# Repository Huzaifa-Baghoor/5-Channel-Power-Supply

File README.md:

# Discreete Dual Output DC Power Supply
This is a Custom Designed 5 Channel DC power supply that provides 15V, 12V, 9V, 5V and 3.3V outputs.

## Working
The circuit takes AC input from Wall Socket and steps it down to 12V then this AC voltage is rectified be 1N4007 Diodes. This 12V DC voltage then goes to a capacitor which decreases the noise and the voltage goes to about 17V. then this voltage is passed through capacitors and zener diodes to provide the 15V, 12V, 9V, 5V and 3.3V outputs.

## Simulation
This Project is Simulated and Tested in Multisim. It worked fine there and supplied constant voltage under Load.

## PCB and Connections
I designed a Custom PCB for this project.

|Schematics|Tracks|
| :---: | :---: |
|  |  |

## 3D Case

I also designed a 3D enclosure box for the project that would have 11 holes, 1 for input and 10 for the outputs.

|View 1|View 2|
| :---: | :---: |
|  |  |

## How to Assemble

To Assemble the PCB, First get the PCB Fabricated and then Solder all the components into their dedicated places.

## BOM

| Name | Purpose | Quantity | Total Cost (USD) | Link | Distributor |
| :---: | :---: | :---: | :---: | :---: | :---: |
| TIP41C | Transistors | 5 | 7 | [TIP41C](https://www.aliexpress.com/item/1005009291854290.html?spm=a2g0o.productlist.main.2.2f5912668WryOQ&algo_pvid=0b7901ac-a991-4423-bff1-2842cce08b4d&algo_exp_id=0b7901ac-a991-4423-bff1-2842cce08b4d-1&pdp_ext_f=%7B%22order%22%3A%223%22%2C%22eval%22%3A%221%22%2C%22fromPage%22%3A%22search%22%7D&pdp_npi=6%40dis%21PKR%212005.10%211963.63%21%21%2143.52%2142.62%21%4021410daa17850251856081765e1e4e%2112000048636612928%21sea%21PK%212961473668%21X%211%210%21n_tag%3A-29919%3Bd%3A7347b7cd%3Bm03_new_user%3A-29895&curPageLogUid=xaTx0ebZWlhw&utparam-url=scene%3Asearch%7Cquery_from%3A%7Cx_object_id%3A1005009291854290%7C_p_origin_prod%3A) | AliExpress |
| Capacitors | Reducing Noise | 11 | 10 |  | AliExpress |
| Resistor | Resistance | 6 | 8 | [Resistor](https://www.aliexpress.com/item/1005006898731441.html?spm=a2g0o.productlist.main.2.5adb174e6BrR4E&algo_pvid=a8b488c6-4e8d-4539-8e68-136df8322c2e&algo_exp_id=a8b488c6-4e8d-4539-8e68-136df8322c2e-1&pdp_ext_f=%7B%22order%22%3A%2218454%22%2C%22spu_best_type%22%3A%22price%22%2C%22eval%22%3A%221%22%2C%22fromPage%22%3A%22search%22%7D&pdp_npi=6%40dis%21PKR%21700.27%21540.04%21%21%2115.19%2111.71%21%40213ba0c517805536286016955e1c85%2112000038655131992%21sea%21PK%212961473668%21X%211%210%21n_tag%3A-29919%3Bd%3A7347b7cd%3Bm03_new_user%3A-29895%3BpisId%3A5000000208499468&curPageLogUid=xK5nH0KMlH7Z&utparam-url=scene%3Asearch%7Cquery_from%3A%7Cx_object_id%3A1005006898731441%7C_p_origin_prod%3A) | AliExpress |
| 12v Transformer | Stepping Down 220V to 12V | 1 | 7 | [12v Transformer](https://www.aliexpress.com/item/1005002190993881.html?spm=a2g0o.productlist.main.3.5ab7c57cYfLk9E&algo_pvid=73899792-524f-4ba5-b0be-0d52e075c67c&algo_exp_id=73899792-524f-4ba5-b0be-0d52e075c67c-2&pdp_ext_f=%7B%22order%22%3A%2269%22%2C%22spu_best_type%22%3A%22price%22%2C%22eval%22%3A%221%22%2C%22fromPage%22%3A%22search%22%7D&pdp_npi=6%40dis%21PKR%212058.51%211933.56%21%21%216.59%216.19%21%40212e520d17805533749515631efcd4%2112000019002828064%21sea%21PK%212961473668%21X%211%210%21n_tag%3A-29919%3Bd%3A7347b7cd%3Bm03_new_user%3A-29895&curPageLogUid=AV8pa8Zxzb4a&utparam-url=scene%3Asearch%7Cquery_from%3A%7Cx_object_id%3A1005002190993881%7C_p_origin_prod%3A) | AliExpress |
| Diode | Rectifier | 1 | 3.6 | [Diode](https://www.aliexpress.com/item/1005012369097375.html?spm=a2g0o.productlist.main.3.e8886f76qmjBun&algo_pvid=c9794048-4184-407d-bd0b-0edbe400970a&algo_exp_id=c9794048-4184-407d-bd0b-0edbe400970a-2&pdp_ext_f=%7B%22order%22%3A%221%22%2C%22eval%22%3A%221%22%2C%22fromPage%22%3A%22search%22%7D&pdp_npi=6%40dis%21PKR%213746.13%211045.14%21%21%2181.26%2122.67%21%40212a70c017805519689011413e223e%2112000058193885987%21sea%21PK%210%21ABX%211%210%21n_tag%3A-29910%3Bd%3A7347b7cd%3Bm03_new_user%3A-29895%3BpisId%3A5000000208221885&curPageLogUid=psqZq8pejmBE&utparam-url=scene%3Asearch%7Cquery_from%3A%7Cx_object_id%3A1005012369097375%7C_p_origin_prod%3A) | AliExpress |
| Zener Diode | Zener Diode | 5 | 15 | [Zener Diode](https://www.aliexpress.com/item/1005010765949748.html?spm=a2g0o.productlist.main.3.547c4dc3FEmVEE&algo_pvid=ed544284-69c7-4d00-983a-87739ac0a65a&algo_exp_id=ed544284-69c7-4d00-983a-87739ac0a65a-2&pdp_ext_f=%7B%22order%22%3A%2211%22%2C%22eval%22%3A%221%22%2C%22fromPage%22%3A%22search%22%7D&pdp_npi=6%40dis%21PKR%218259.05%213964.12%21%21%21179.26%2186.04%21%40210159d417850253732154640e0e3d%2112000053435372829%21sea%21PK%212961473668%21X%211%210%21n_tag%3A-29919%3Bd%3A7347b7cd%3Bm03_new_user%3A-29895&curPageLogUid=iE0PDDcbkAz3&utparam-url=scene%3Asearch%7Cquery_from%3A%7Cx_object_id%3A1005010765949748%7C_p_origin_prod%3A) | AliExpress |

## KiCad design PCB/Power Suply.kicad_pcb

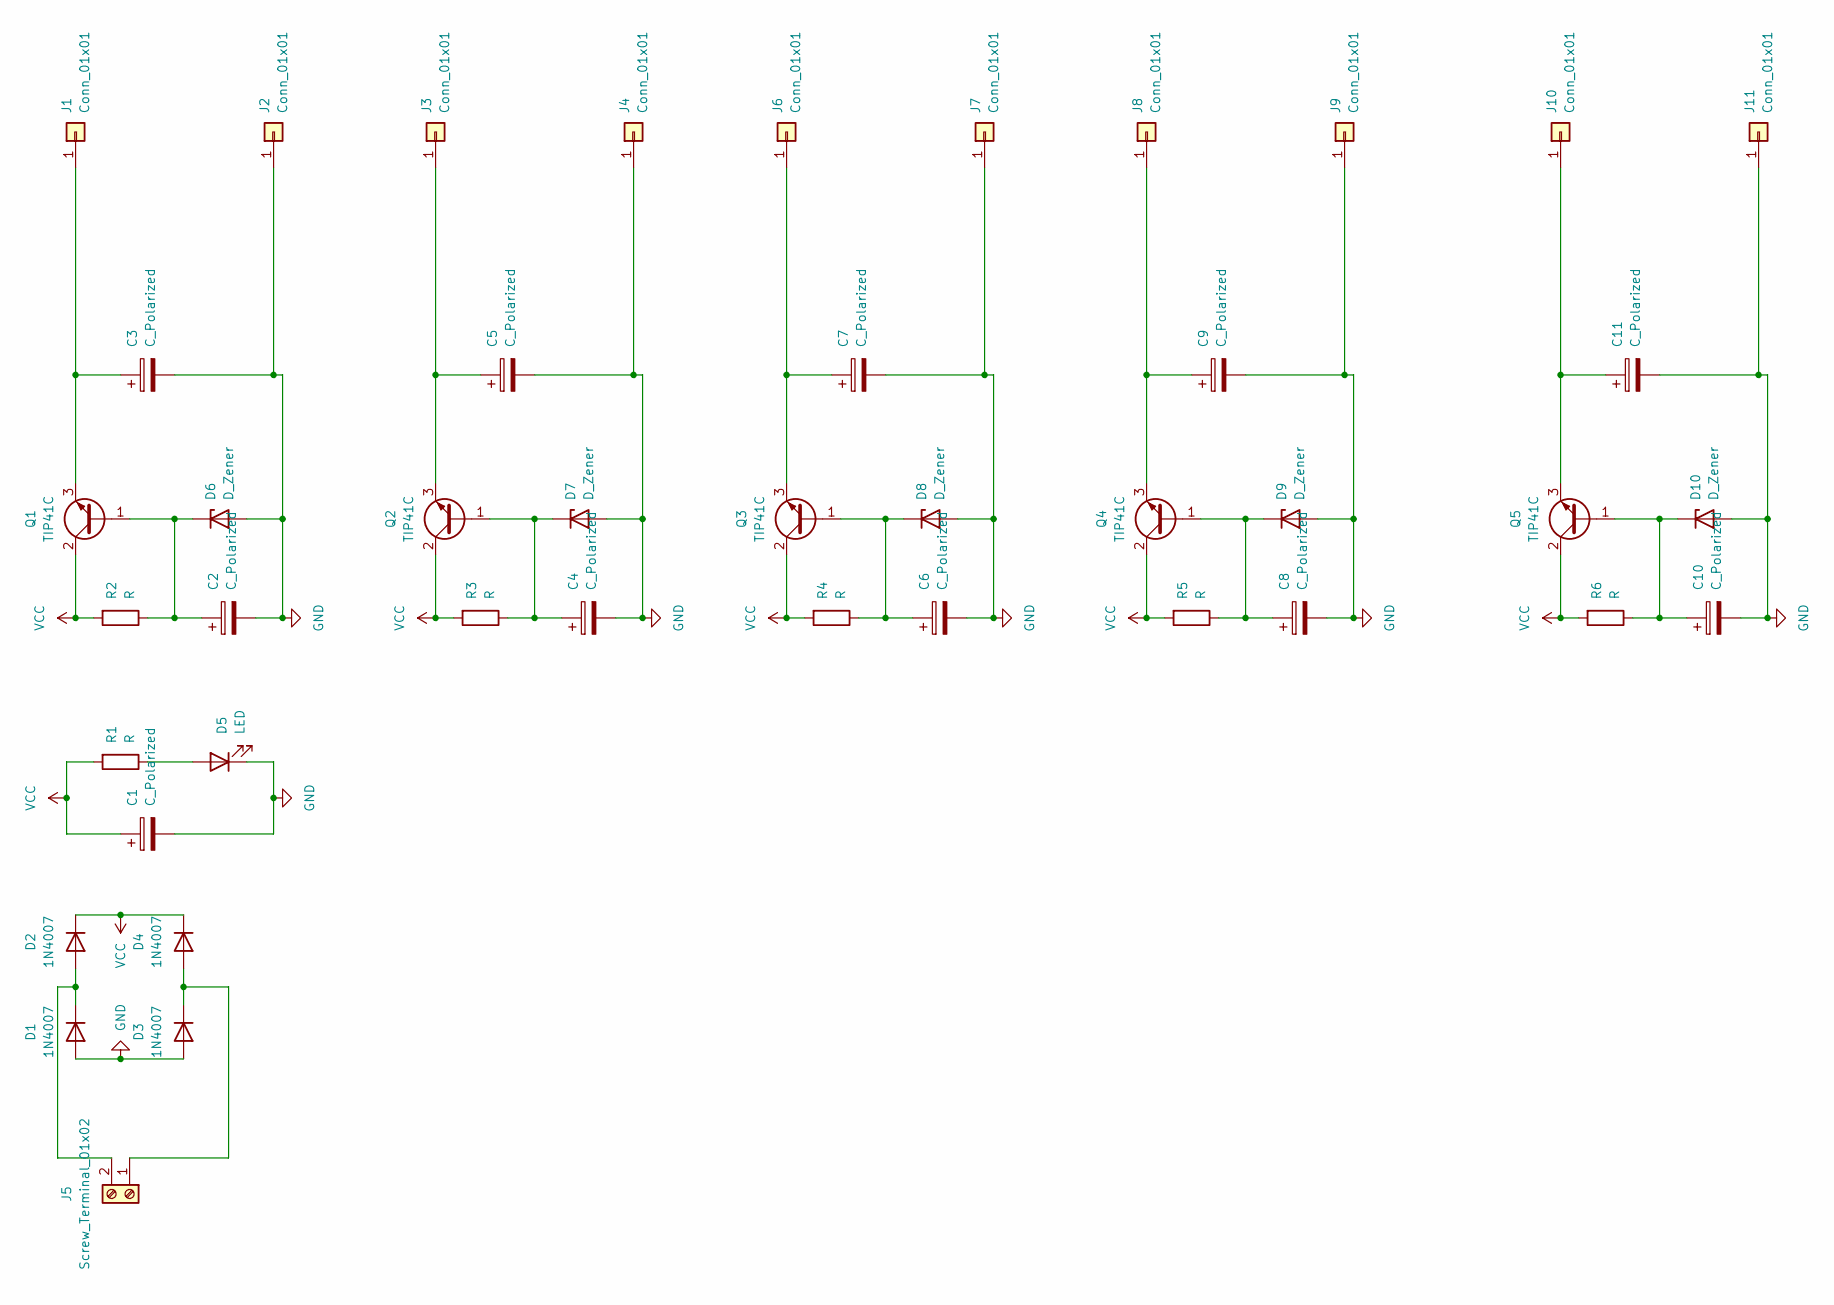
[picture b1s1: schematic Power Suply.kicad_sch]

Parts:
C1, C2, C3, C4, C5, C6, C7, C8, C9, C10, C11: C_Polarized; CP_Radial_D10.0mm_P5.00mm
D1, D2, D3, D4: 1N4007; D_DO-41_SOD81_P10.16mm_Horizontal
D5: LED; LED_D5.0mm
D6, D7, D8, D9, D10: D_Zener; D_DO-41_SOD81_P10.16mm_Horizontal
J1, J2, J3, J4, J6, J7, J8, J9, J10, J11: Conn_01x01; Banana_Jack_1Pin
J5: Screw_Terminal_01x02; TerminalBlock_Phoenix_MKDS-1,5-2-5.08_1x02_P5.08mm_Horizont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
Q1, Q2, Q3, Q4, Q5: TIP41C; TO-220-3_Vertical
R1, R2, R3, R4, R5, R6: R; R_Axial_DIN0207_L6.3mm_D2.5mm_P7.62mm_Horizontal

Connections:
GND: C1.2, C2.2, C3.2, C4.2, C5.2, C6.2, C7.2, C8.2, C9.2, C10.2, C11.2, D1.2 (A), D3.2 (A), D5.1 (K), D6.2 (A), D7.2 (A), D8.2 (A), D9.2 (A), D10.2 (A), J2.1, J4.1, J7.1, J9.1, J11.1
unnamed: D1.1 (K), D2.2 (A), J5.2
unnamed: D3.1 (K), D4.2 (A), J5.1
unnamed: D5.2 (A), R1.1
unnamed: C2.1, D6.1 (K), Q1.1 (B), R2.1
unnamed: C4.1, D7.1 (K), Q2.1 (B), R3.1
unnamed: C6.1, D8.1 (K), Q3.1 (B), R4.1
unnamed: C8.1, D9.1 (K), Q4.1 (B), R5.1
unnamed: C10.1, D10.1 (K), Q5.1 (B), R6.1
unnamed: C3.1, J1.1, Q1.3 (E)
unnamed: C5.1, J3.1, Q2.3 (E)
unnamed: C7.1, J6.1, Q3.3 (E)
unnamed: C9.1, J8.1, Q4.3 (E)
unnamed: C11.1, J10.1, Q5.3 (E)
VCC: C1.1, D2.1 (K), D4.1 (K), Q1.2 (C), Q2.2 (C), Q3.2 (C), Q4.2 (C), Q5.2 (C), R1.2, R2.2, R3.2, R4.2, R5.2, R6.2

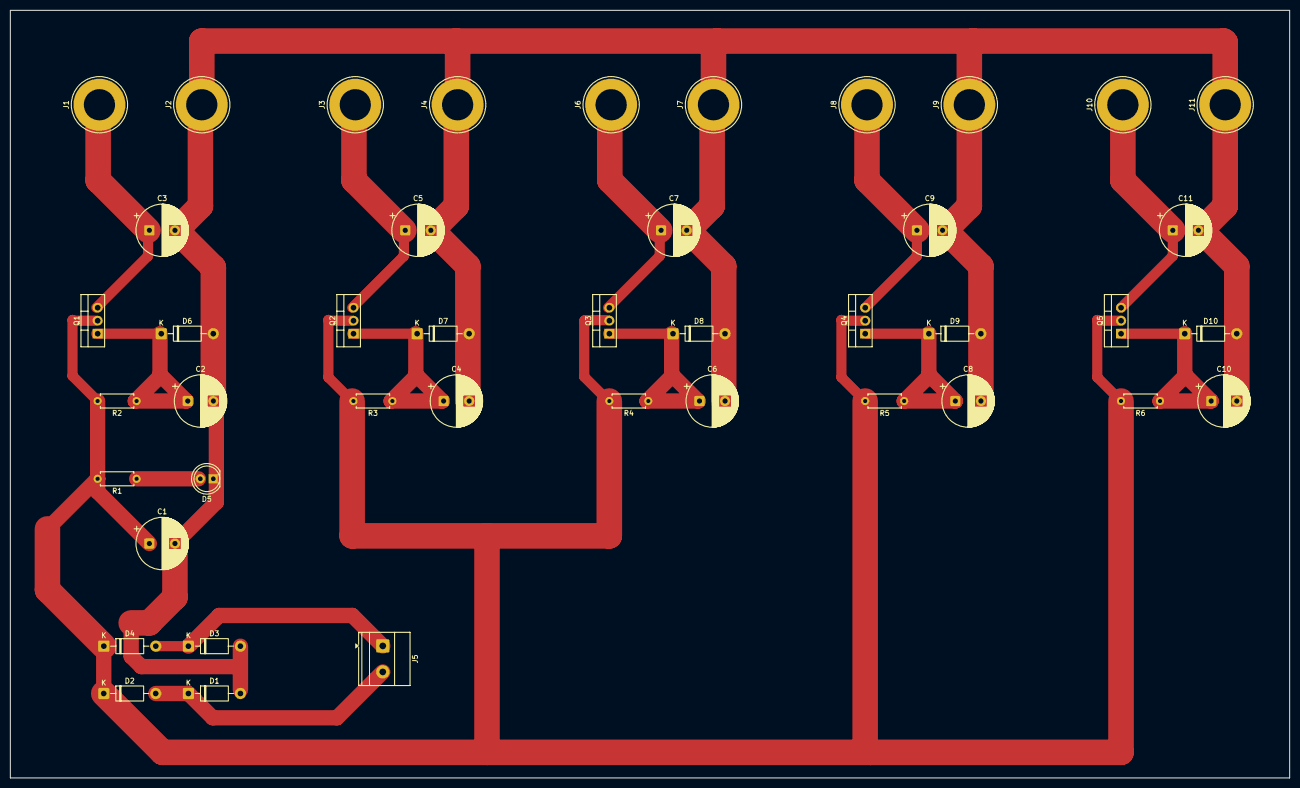
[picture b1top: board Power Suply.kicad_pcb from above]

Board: 2 copper layers, 250.0 x 150.0 mm, 43 parts (0 on the bottom side), 15 nets.
